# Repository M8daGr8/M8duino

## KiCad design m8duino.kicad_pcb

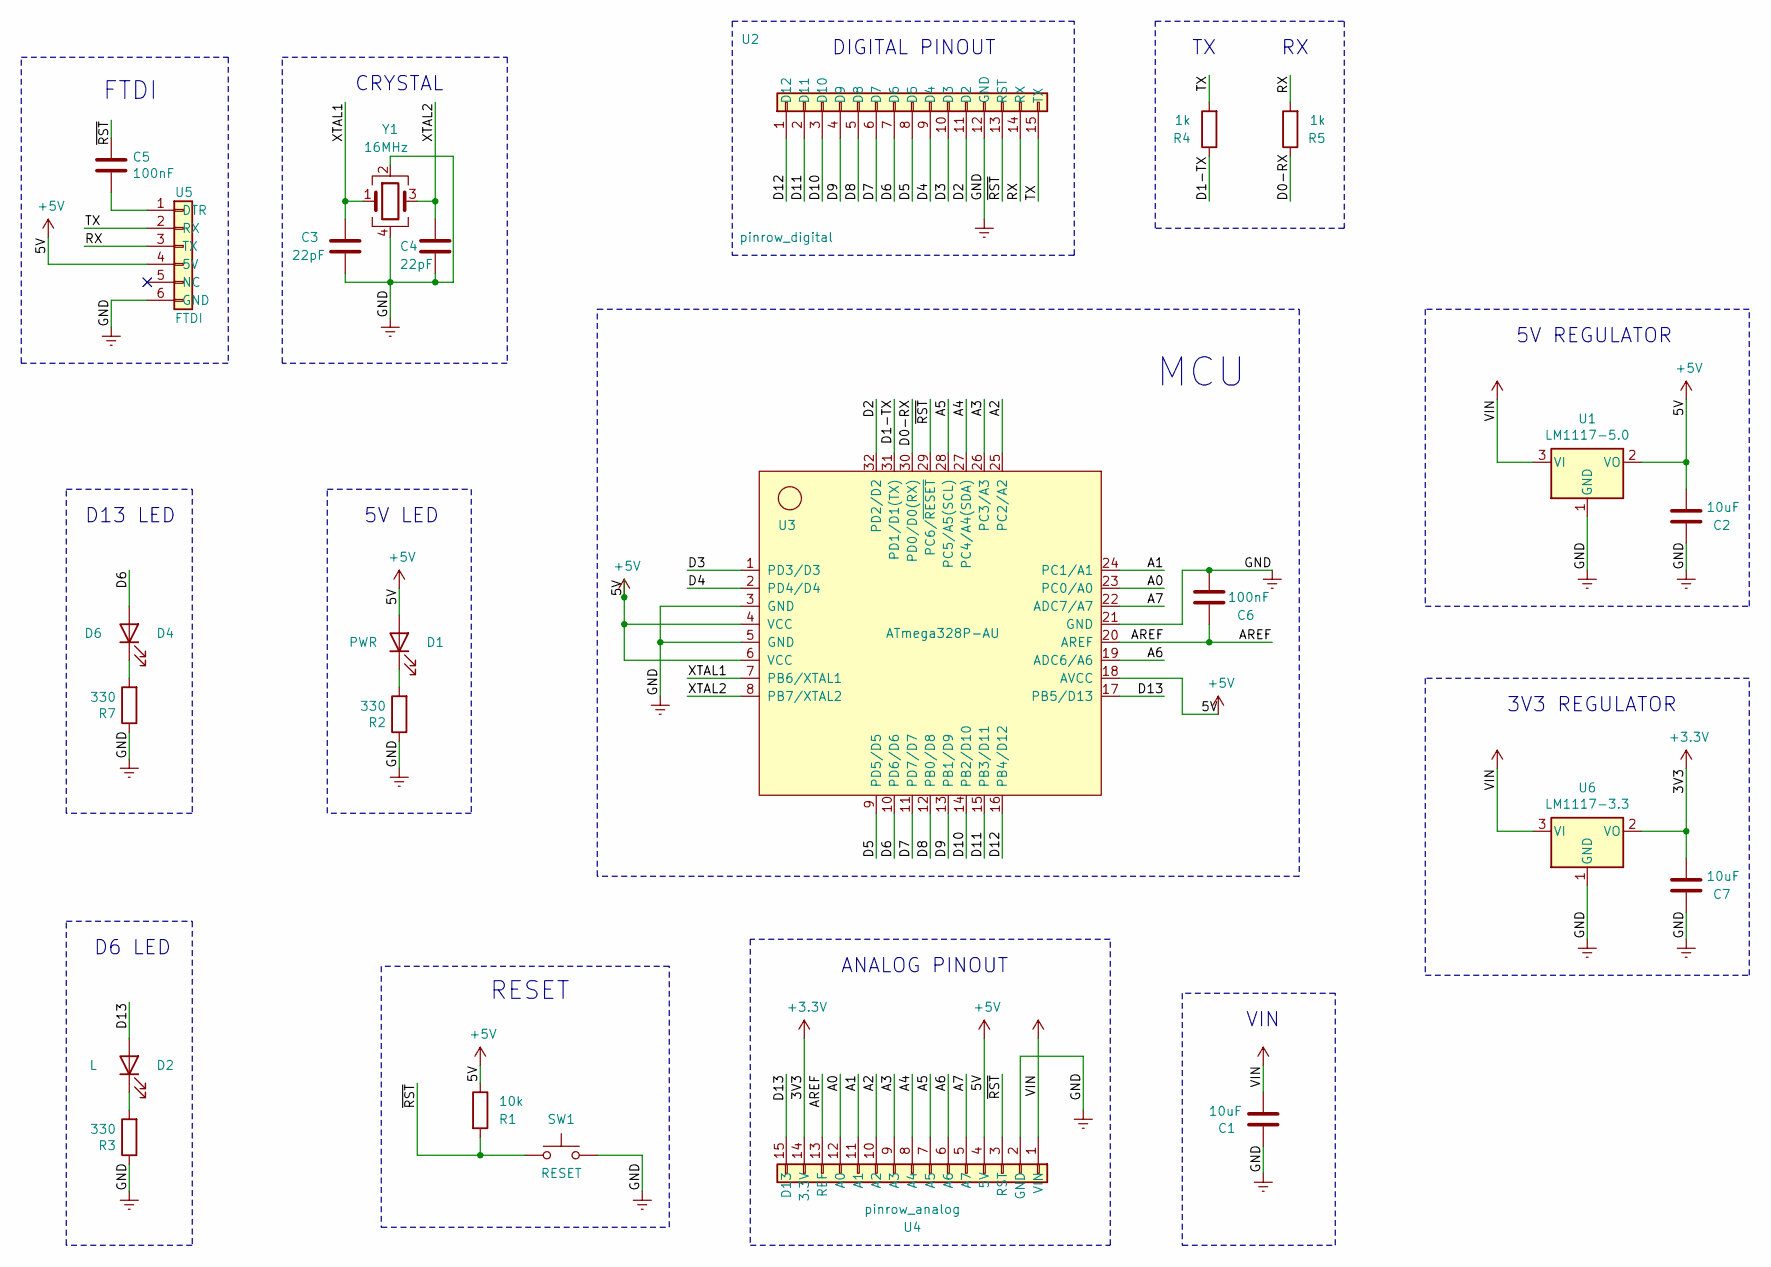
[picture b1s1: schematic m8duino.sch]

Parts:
C1, C2, C7: 10uF; C_0805_2012Metric_Pad1.15x1.40mm_HandSolder
C3, C4: 22pF; C_0805_2012Metric_Pad1.15x1.40mm_HandSolder
C5, C6: 100nF; C_0805_2012Metric_Pad1.15x1.40mm_HandSolder
D1: PWR; LED_0805_2012Metric_Pad1.15x1.40mm_HandSolder
D2: L; LED_0805_2012Metric_Pad1.15x1.40mm_HandSolder
D4: D6; LED_0805_2012Metric_Pad1.15x1.40mm_HandSolder
R1: 10k; R_0805_2012Metric_Pad1.15x1.40mm_HandSolder
R2, R3, R7: 330; R_0805_2012Metric_Pad1.15x1.40mm_HandSolder
R4, R5: 1k; R_0805_2012Metric_Pad1.15x1.40mm_HandSolder
SW1: RESET; SW_Push_1P1T_NO_6x6mm_H9.5mm
U1: LM1117-5.0; SOT-223-3_TabPin2
U2: pinrow_digital; PinHeader_1x15_P2.54mm_Vertical
U3: ATmega328P-AU; TQFP-32_7x7mm_P0.8mm
U4: pinrow_analog; PinHeader_1x15_P2.54mm_Vertical
U5: FTDI; PinSocket_1x06_P2.54mm_Vertical
U6: LM1117-3.3; SOT-223-3_TabPin2
Y1: 16MHz; Crystal_SMD_EuroQuartz_MJ-4Pin_5.0x3.2mm_HandSoldering

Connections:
+3V3: C7.2, U4.14 (3.3V), U6.2 (VO)
+5V: C2.2, D1.2 (A), R1.1, U1.2 (VO), U3.4 (VCC), U3.6 (VCC), U3.18 (AVCC), U4.4 (5V), U5.4 (5V)
/A0: U3.23 (PC0/A0), U4.12 (A0)
/A1: U3.24 (PC1/A1), U4.11 (A1)
/A2: U3.25 (PC2/A2), U4.10 (A2)
/A3: U3.26 (PC3/A3), U4.9 (A3)
/A4: U3.27 (PC4/A4(SDA)), U4.8 (A4)
/A5: U3.28 (PC5/A5(SCL)), U4.7 (A5)
/A6: U3.19 (ADC6/A6), U4.6 (A6)
/A7: U3.22 (ADC7/A7), U4.5 (A7)
/AREF: C6.2, U3.20 (AREF), U4.13 (REF)
/D0-RX: R5.1, U3.30 (PD0/D0(RX))
/D1-TX: R4.1, U3.31 (PD1/D1(TX))
/D2: U2.11 (D2), U3.32 (PD2/D2)
/D3: U2.10 (D3), U3.1 (PD3/D3)
/D4: U2.9 (D4), U3.2 (PD4/D4)
/D5: U2.8 (D5), U3.9 (PD5/D5)
/D6: D4.2 (A), U2.7 (D6), U3.10 (PD6/D6)
/D7: U2.6 (D7), U3.11 (PD7/D7)
/D8: U2.5 (D8), U3.12 (PB0/D8)
/D9: U2.4 (D9), U3.13 (PB1/D9)
/D10: U2.3 (D10), U3.14 (PB2/D10)
/D11: U2.2 (D11), U3.15 (PB3/D11)
/D12: U2.1 (D12), U3.16 (PB4/D12)
/D13: D2.2 (A), U3.17 (PB5/D13), U4.15 (D13)
/RX: R5.2, U2.14 (RX), U5.3 (TX)
/TX: R4.2, U2.15 (TX), U5.2 (RX)
/XTAL1: C3.1, U3.7 (PB6/XTAL1), Y1.1
/XTAL2: C4.1, U3.8 (PB7/XTAL2), Y1.3
/~RST: C5.1, R1.2, SW1.1, U2.13 (RST), U3.29 (PC6/~RESET~), U4.3 (RST)
Earth: C1.1, C2.1, C3.2, C4.2, C6.1, C7.1, R2.1, R3.1, R7.1, SW1.2, U1.1 (GND), U2.12 (GND), U3.3 (GND), U3.5 (GND), U3.21 (GND), U4.2 (GND), U5.6 (GND), U6.1 (GND), Y1.2, Y1.4
unnamed: C5.2, U5.1 (DTR)
unnamed: D1.1 (K), R2.2
unnamed: D2.1 (K), R3.2
unnamed: D4.1 (K), R7.2
VCC: C1.2, U1.3 (VI), U4.1 (VIN), U6.3 (VI)

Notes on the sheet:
5V REGULATOR
FTDI
RESET
DIGITAL PINOUT
3V3 REGULATOR
CRYSTAL
ANALOG PINOUT
5V LED
D6 LED
MCU
VIN
TX RX
D13 LED

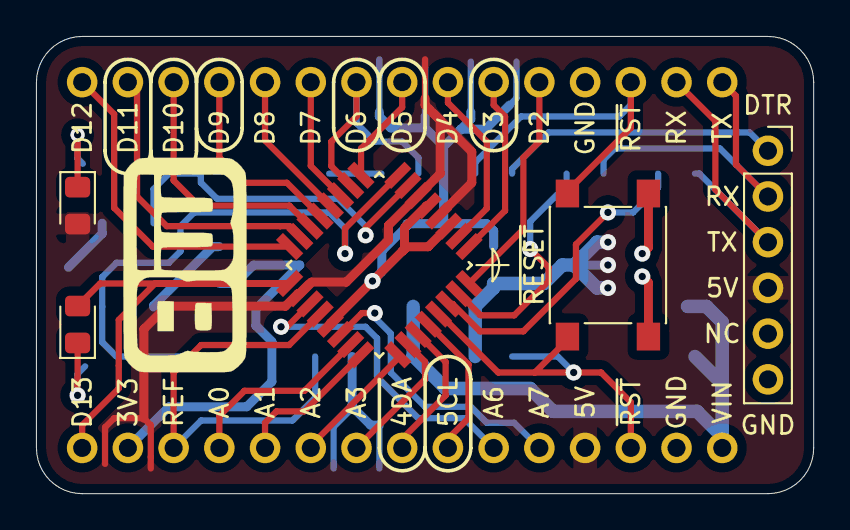
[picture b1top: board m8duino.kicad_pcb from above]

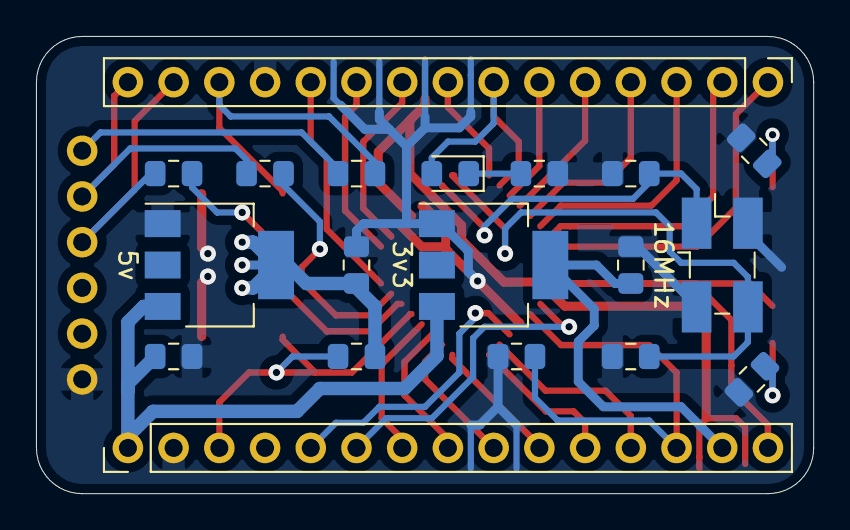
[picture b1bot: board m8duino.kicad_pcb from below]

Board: 2 copper layers, 43.2 x 25.4 mm, 24 parts (19 on the bottom side), 36 nets.
